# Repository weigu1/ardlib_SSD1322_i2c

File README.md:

# Arduino library for SSD1322 (parallel mode) over I2C

## Some infos

OLED displays are getting cheaper. They need less power, are brighter and have a greater temperature range then LCDs.
At <http://mouser.com> I found an 128x64 monochrome display from Newhaven with 2.7' to possibly replace the GTK-281.

The display can be used in parallel mode or over SPI. As I needed I2C I modified the [parallel to I2C board from the GTK281](https://www.weigu.lu/microcontroller/ardlib_NT7534_I2C/index.html) PCB to use it for the new display.

The display is working like a charm, but it is quite slow.

## All infos on: <https://www.weigu.lu/microcontroller/ardlib_SSD1322_I2C/index.html>

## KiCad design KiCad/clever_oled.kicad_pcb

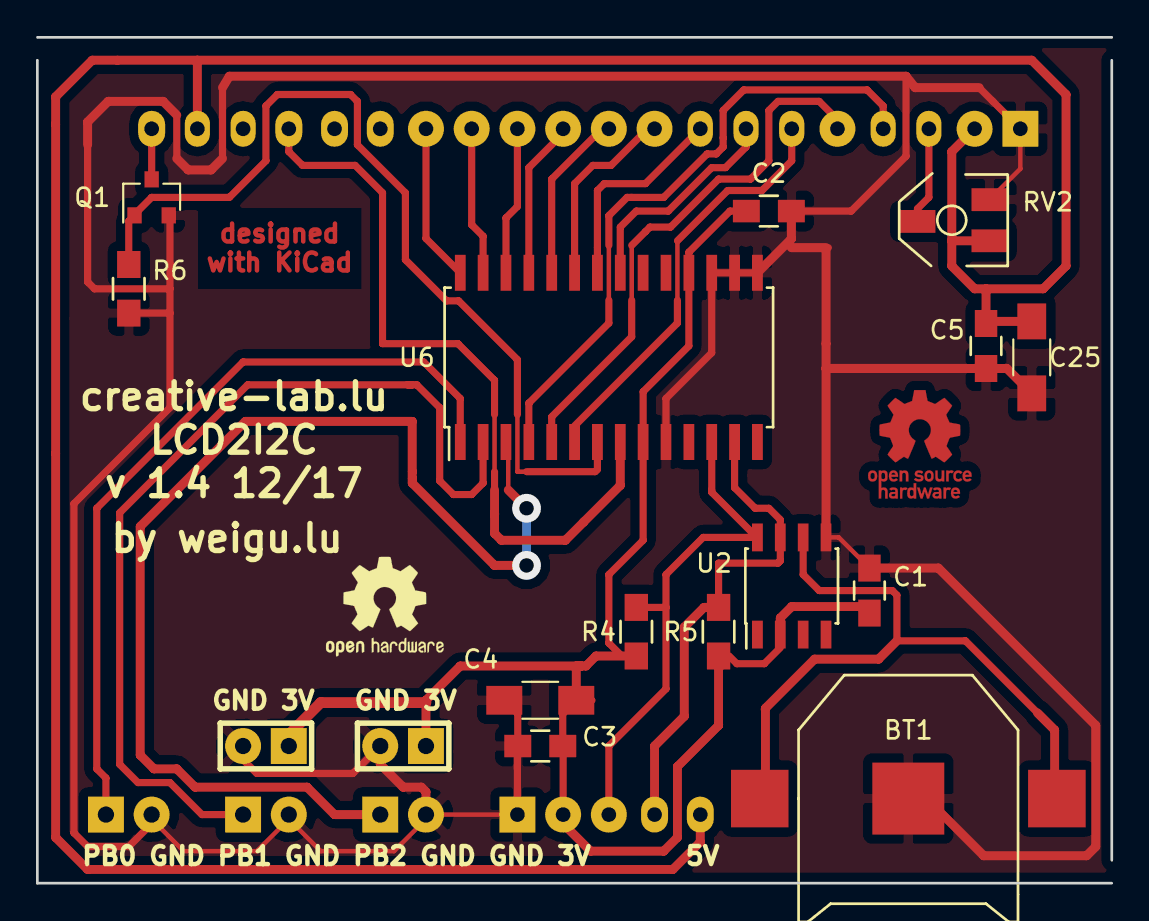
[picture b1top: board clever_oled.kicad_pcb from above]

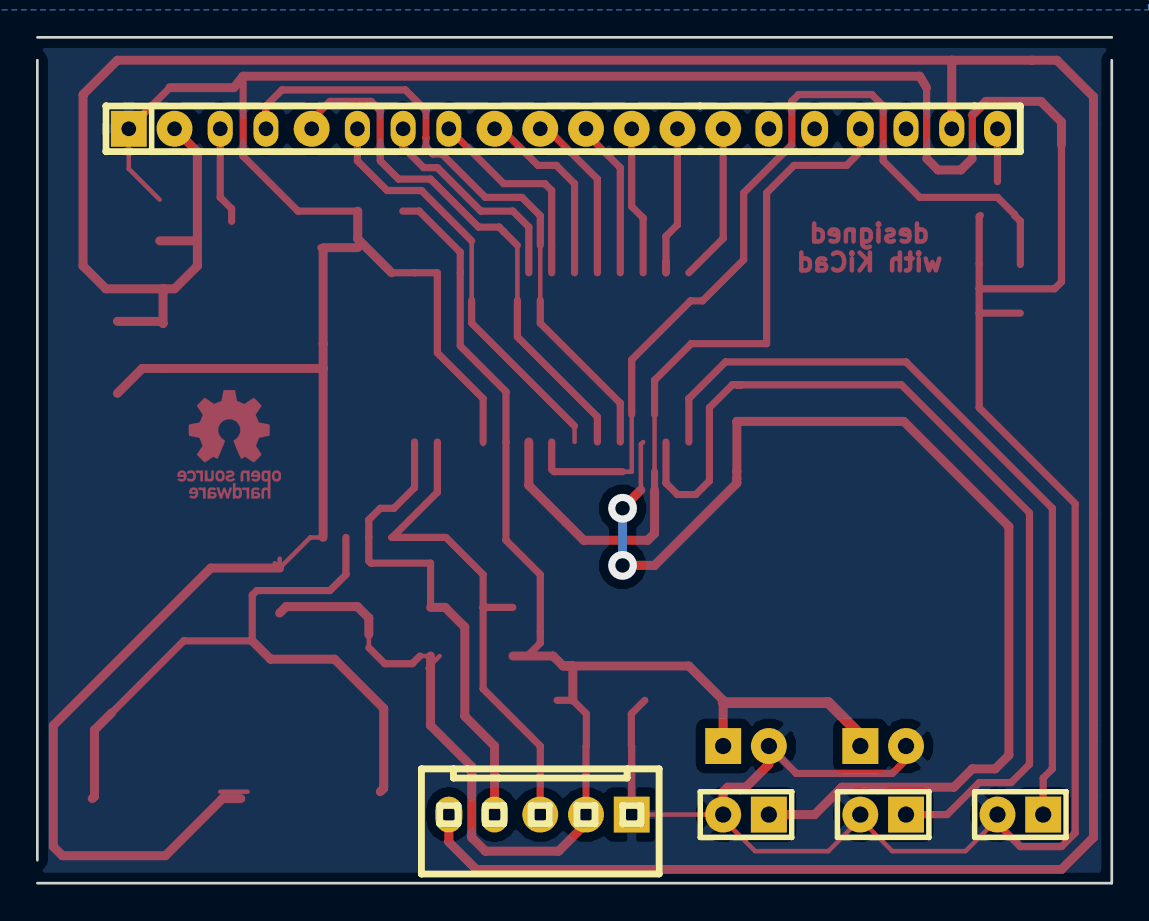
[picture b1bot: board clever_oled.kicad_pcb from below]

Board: 2 copper layers, 59.7 x 47.0 mm, 21 parts (5 on the bottom side), 24 nets.

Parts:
BT1: BAT 3V; WCR2025_SMD
C1, C2, C3, C5: 100nF; C_0805_HandSoldering
C4, C25: 10uF; C_1206_HandSoldering
J1, J2: SIL1x2L; WSIL2
J4: I2C; WSIL5_SL
J5: PB0; WSIL2
J6: PB1; WSIL2
J7: PB2; WSIL2
J8: GTK-281; WSIL20
Q1: 2N7002; SOT-23
R4, R5: 1.8k; R_0805_HandSoldering
R6: 100k; R_0805_HandSoldering
RV2: 10k; WPOT_SMD
U2: DS3231MZ+; SOIC-8_3.9x4.9mm_Pitch1.27mm
U6: W_MCP23017; SOIC-28W_7.5x17.9mm_Pitch1.27mm

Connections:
GND: BT1.2, C1.2, C2.2, C3.2, C4.2, C5.1, C25.1, J1.2, J2.2, J4.1, J5.2, J6.2, J7.2, J8.1, Q1.2, R6.2, RV2.3, U2.5, U6.10, U6.15, U6.16, U6.17
unnamed: BT1.1, U2.6
unnamed: C5.2, C25.2, J4.5, J8.2, J8.19, RV2.1
unnamed: J4.3, R4.2, U2.8, U6.12
unnamed: J4.4, R5.2, U2.7, U6.13
unnamed: J5.1, U6.1
unnamed: J6.1, U6.2
unnamed: J7.1, U6.3
unnamed: J8.3, RV2.2
unnamed: J8.4, U6.4
unnamed: J8.5, U6.5
unnamed: J8.6, U6.6
unnamed: J8.7, U6.21
unnamed: J8.8, U6.22
unnamed: J8.9, U6.23
unnamed: J8.10, U6.24
unnamed: J8.11, U6.25
unnamed: J8.12, U6.26
unnamed: J8.13, U6.27
unnamed: J8.14, U6.28
unnamed: J8.17, U6.8
unnamed: J8.20, Q1.3
unnamed: Q1.1, R6.1, U6.7
VCC: C1.1, C2.1, C3.1, C4.1, J1.1, J2.1, J4.2, R4.1, R5.1, U2.2, U6.9, U6.18

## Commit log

2022-09-09 added picture
